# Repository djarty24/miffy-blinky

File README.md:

# miffy-blinky! 🐰✨

This is my first PCB project. I made a custom Miffy-shaped blinky keychain following Hack Club's Stasis project started guide! 

Coming from mostly web dev and frontend stuff, jumping into KiCad was definitely an experience. It turns out making a PCB is basically like doing UI design, except the components actually take up physical space and you can't just z index them away lol. 

### What I learned
* I learned how to physically route components on the PCB.
* I imported a custom DXF drawing for Miffy's face, but it wouldn't show up in the 3D viewer. Turns out CAD lines have a 0mm thickness by default, so I had to manually set the ink to 0.2mm so the factory actually prints it!
* Drawing the copper tracks is honestly like a puzzle game. You can't cross a front wire over another front wire without shorting the board, but you can drop a pin and draw on the back layer to go underneath. 

Super proud of how this turned out!

## Journal

I finally finished my first ever custom hardware project! I made a PCB shaped like Miffy, one of my favorite characters, that also doubles as a keychain.

## Schematic
The first step is in the schematic editor of KiCad to design the circuit. Here, I placed symbols for the 555 timer, a 4017 counter, a power bank, two capacitors, two resistors, and 10 LEDs.

In my Principles of Engineering class in school, we briefly covered circuitry, but I was under the assumption that everything needs to be connected. However, something cool I learned was using labels. This kept my schematic design cleaner and more readable.

## Footprints
I followed the guide to add the custom 4017 counter footprint to my project. Then, I switched to the PCB view, only to find that I couldn't actually move the LEDs. After a lot of troubleshooting, I realized that I hadn't added any footprints for the rest of my components like the actual LEDs.

## PCB Design
This was the most fun part!

### Positioning
Now that the footprints were installed, I uploaded a DXF file of Miffy. I learned about grouping and ungrouping and how to set each part of her face on the correct layer. I changed the border to be an Edge Cut for the outline of the PCB. Then, I placed the components and LEDs where I wanted on the board.

### Copper Wiring
Now that everything was positioned where I wanted it to be, I had to replace the ratsnets with copper tracks. This was both therapeutic and frustrating at times because you can't have two lines of the same color cross. When a red track blocked my path, I switched to the blue layer and vice versa.

The Design Rules Checker tool was extremely helpful because it helped me catch mistakes I made.

Finally, I added another hole from the Edge Cuts layer with a diameter of 1.5 mm to serve as the hole where I can insert my keychain later. I also converted Miffy's eyes and mouth into Polygons (this took a lot longer than expected) and filled them in.

## Gerbers
This was the last step, I just generated the gerber and drill files and saved them into a zip. Then, I went to JLCPCB to get a price estimate. I changed the color of my PCB to white, and so the drawings turned black, so it actually looks pretty similar to the original Miffy character!

I also pushed my files to GitHub and wrote up a quick README for my project.

## Final Thoughts
This was my first time working with PCBs and it was an awesome experience. Designing a physical object that I can hold in my hands is completely different from anything I've done before since I usually just write software. I learned a lot about designing readable schematics and positioning them on the actual PCB.

Even though there was a huge learning curve and a fair share of frustrating moments, I learned a lot and it was really fun!

I had so much fun building this Miffy blinky keychain and I'm definitely going to design more PCBs in the future!

---
<div align="center">

### This project was made for Hack Club's Stasis event.
</div>

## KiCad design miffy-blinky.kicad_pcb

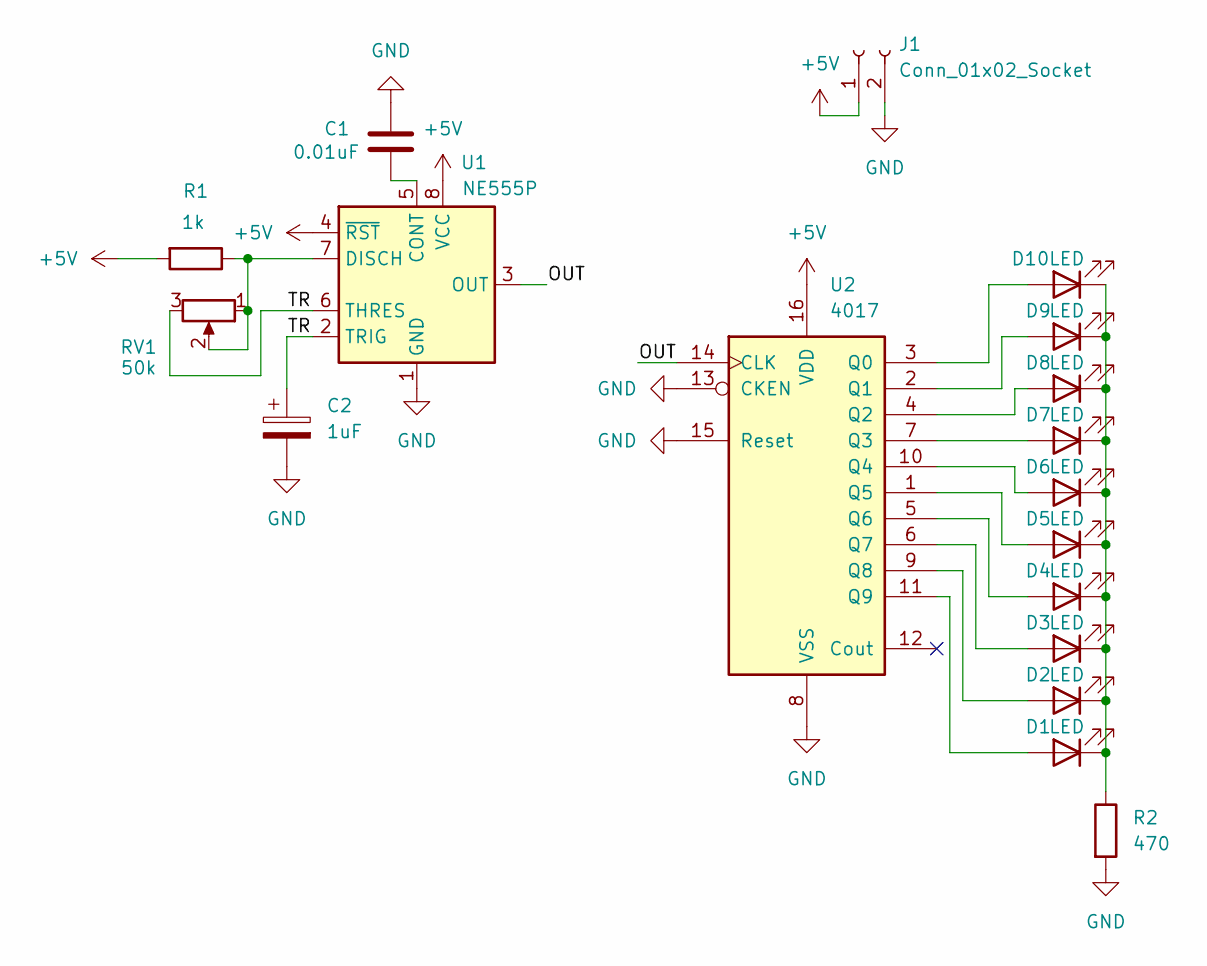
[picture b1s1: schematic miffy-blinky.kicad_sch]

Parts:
C1: 0.01uF
C2: 1uF
D1, D2, D3, D4, D5, D6, D7, D8, D9, D10: LED
J1: Conn_01x02_Socket
R1: 1k
R2: 470
RV1: 50k
U1: NE555P; DIP-8_W7.62mm
U2: 4017; N16

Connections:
+5V: J1.1, R1.2, U1.4 (~RST), U1.8 (VCC), U2.16 (VDD)
/OUT: U1.3 (OUT), U2.14 (CLK)
/TR: C2.1, RV1.3, U1.2 (TRIG), U1.6 (THRES)
GND: C1.1, C2.2, J1.2, R2.2, U1.1 (GND), U2.8 (VSS), U2.13 (CKEN), U2.15 (Reset)
unnamed: D1.2 (A), U2.11 (Q9)
unnamed: D1.1 (K), D2.1 (K), D3.1 (K), D4.1 (K), D5.1 (K), D6.1 (K), D7.1 (K), D8.1 (K), D9.1 (K), D10.1 (K), R2.1
unnamed: D2.2 (A), U2.9 (Q8)
unnamed: D3.2 (A), U2.6 (Q7)
unnamed: D4.2 (A), U2.5 (Q6)
unnamed: D5.2 (A), U2.1 (Q5)
unnamed: D6.2 (A), U2.10 (Q4)
unnamed: D7.2 (A), U2.7 (Q3)
unnamed: D8.2 (A), U2.4 (Q2)
unnamed: D9.2 (A), U2.2 (Q1)
unnamed: D10.2 (A), U2.3 (Q0)
unnamed: C1.2, U1.5 (CONT)
unnamed: R1.1, RV1.1, RV1.2, U1.7 (DISCH)

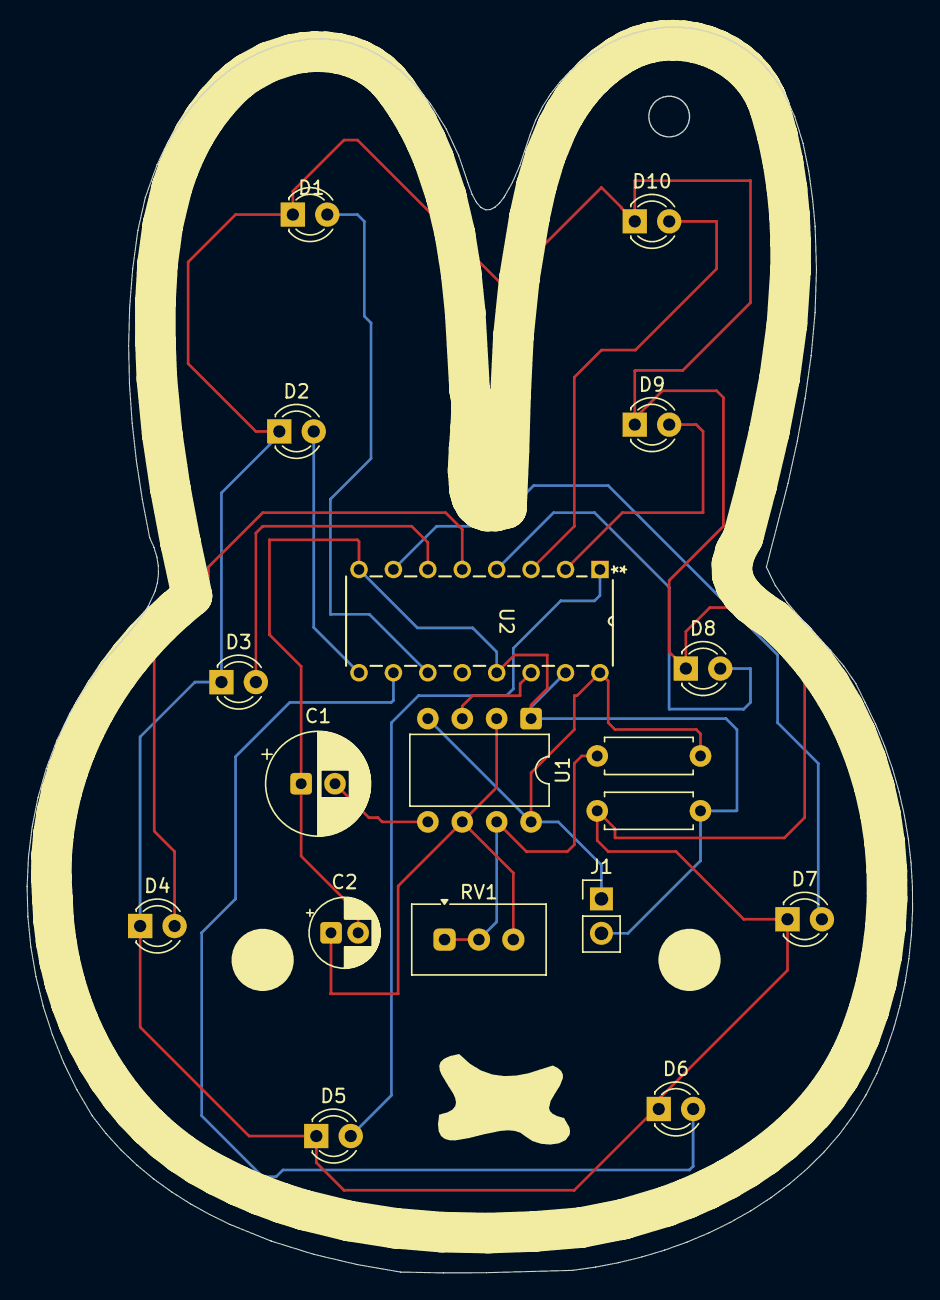
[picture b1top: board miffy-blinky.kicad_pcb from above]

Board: 2 copper layers, 65.3 x 91.9 mm, 18 parts (0 on the bottom side), 17 nets.

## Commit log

2026-04-18 Add project title and description to README
2026-04-18 finished miffy pcb design from starter project tutorial
2026-04-18 added gitignore to make it easier
2026-04-18 added keychain hole and updated gerbers
2026-04-28 Enhance README with project details and insights
    Added detailed project journal, schematic, footprints, PCB design, Gerbers, and final thoughts sections to README.
